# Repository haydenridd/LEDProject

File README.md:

# LEDProject
Repository for LED controller.

Casey if you're reading this yes it's the right repo.

If this worked then I sort of understand how to use this tool

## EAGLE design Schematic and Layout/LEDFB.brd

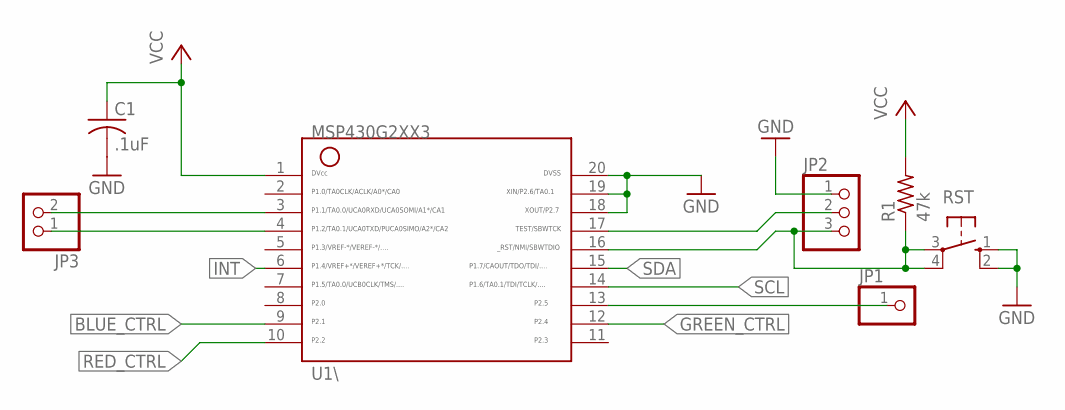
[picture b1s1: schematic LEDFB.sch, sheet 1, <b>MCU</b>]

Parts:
C1: .1uF; C0805
JP1: PINHD-1X1; 1X01
JP2: PINHD-1X3; 1X03
JP3: PINHD-1X2; 1X02
R1: 47k; R0805
RST: 10-XX; B3F-10XX
U1\: G2XX3---PW20; PW20

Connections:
BLUE_CTRL: U1\.9; also elsewhere on the board
GND: C1.2, JP2.1, RST.1 (S), RST.2 (S1), U1\.18, U1\.19, U1\.20; also elsewhere on the board
GREEN_CTRL: U1\.12; also elsewhere on the board
INT: U1\.6; also elsewhere on the board
unnamed: JP3.2, U1\.3
unnamed: JP3.1, U1\.4
unnamed: JP1.1, U1\.13
unnamed: JP2.2, U1\.17
unnamed: JP2.3, R1.1, RST.3, RST.4 (P1), U1\.16
RED_CTRL: U1\.10; also elsewhere on the board
SCL: U1\.14; also elsewhere on the board
SDA: U1\.15; also elsewhere on the board
VCC: C1.1, R1.2, U1\.1; also elsewhere on the board

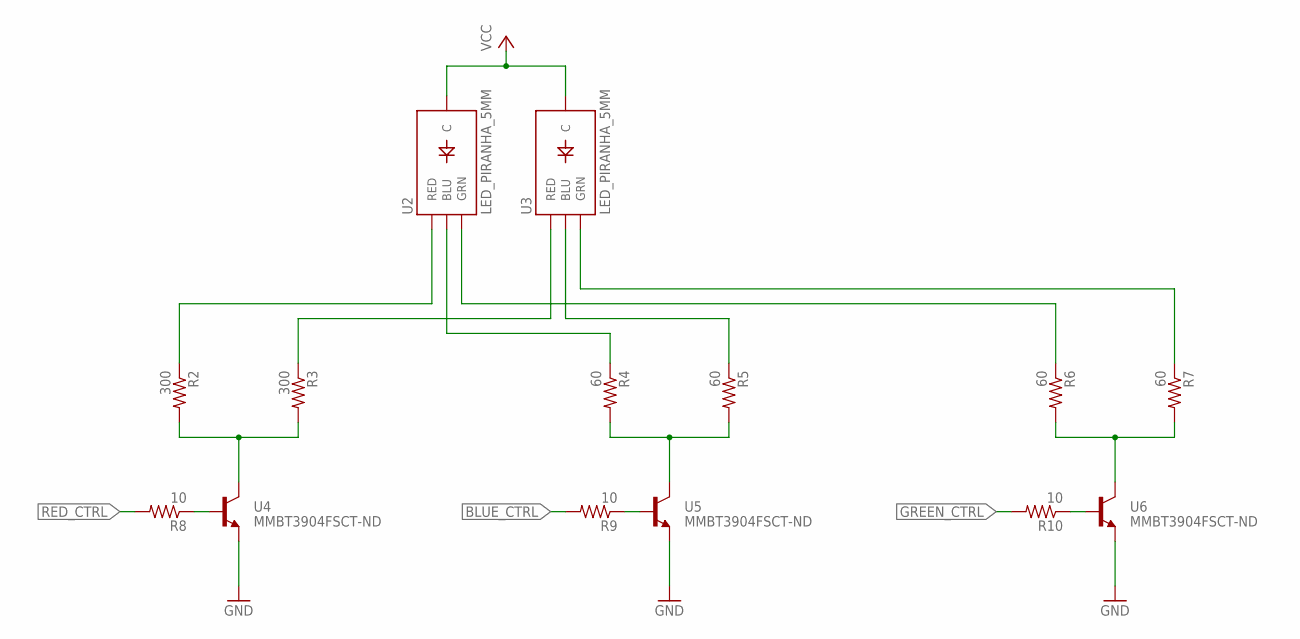
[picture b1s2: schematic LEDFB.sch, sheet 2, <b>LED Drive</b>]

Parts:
R2, R3: 300; R0805
R4, R5, R6, R7: 60; R0805
R8, R9, R10: 10; R0805
U2, U3: LED_PIRANHA_5MM
U4, U5, U6: MMBT3904FSCT-ND; SOT-23

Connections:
BLUE_CTRL: R9.2; also elsewhere on the board
GND: U4.2 (E), U5.2 (E), U6.2 (E); also elsewhere on the board
GREEN_CTRL: R10.2; also elsewhere on the board
unnamed: R2.1, U2.R (RED)
unnamed: R3.1, U3.R (RED)
unnamed: R2.2, R3.2, U4.3 (C)
unnamed: R4.1, U2.B (BLU)
unnamed: R8.1, U4.1 (B)
unnamed: R9.1, U5.1 (B)
unnamed: R10.1, U6.1 (B)
unnamed: R5.1, U3.B (BLU)
unnamed: R4.2, R5.2, U5.3 (C)
unnamed: R6.2, R7.2, U6.3 (C)
unnamed: R6.1, U2.G (GRN)
unnamed: R7.1, U3.G (GRN)
RED_CTRL: R8.2; also elsewhere on the board
VCC: U2.C, U3.C; also elsewhere on the board

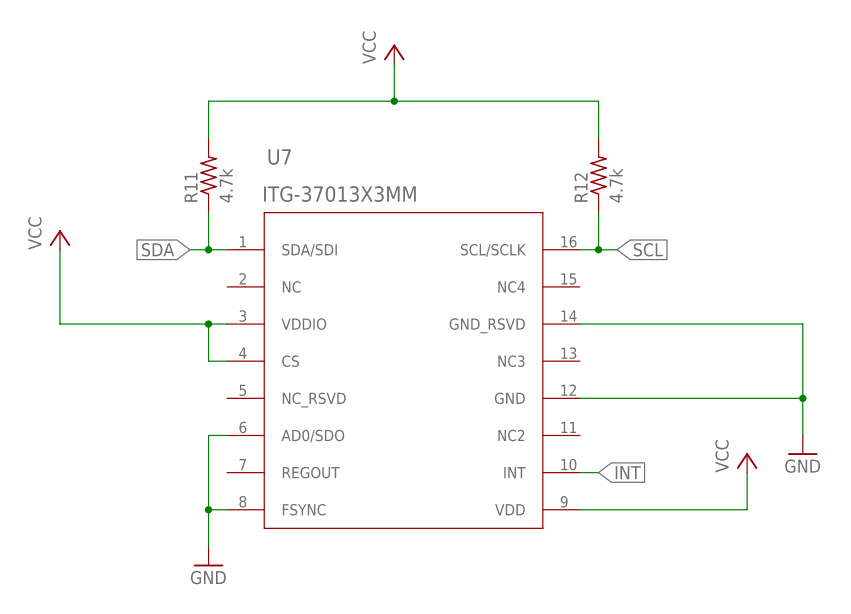
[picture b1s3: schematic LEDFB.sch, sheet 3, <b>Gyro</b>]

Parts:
R11, R12: 4.7k; M0805
U7: ITG-37013X3MM; QFN-16

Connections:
GND: U7.6 (AD0/SDO), U7.8 (FSYNC), U7.12 (GND), U7.14 (GND_RSVD); also elsewhere on the board
INT: U7.10 (INT); also elsewhere on the board
NC3: U7.13 (NC3)
NC4: U7.15 (NC4)
NC_RSVD: U7.5 (NC_RSVD)
SCL: R12.1, U7.16 (SCL/SCLK); also elsewhere on the board
SDA: R11.1, U7.1 (SDA/SDI); also elsewhere on the board
VCC: R11.2, R12.2, U7.3 (VDDIO), U7.4 (CS), U7.9 (VDD); also elsewhere on the board

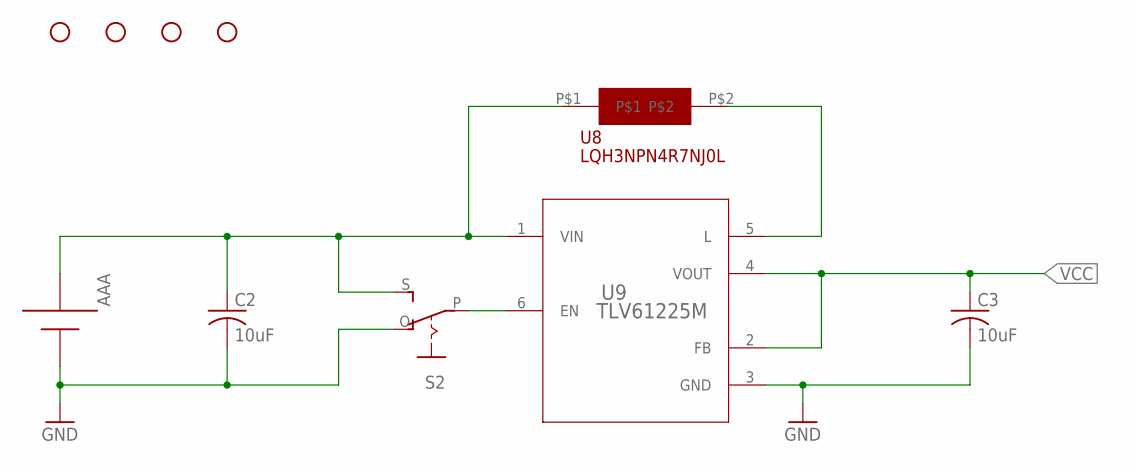
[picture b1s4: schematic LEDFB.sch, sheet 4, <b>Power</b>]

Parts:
AAA: AAA; 12BH412
C2, C3: 10uF; C0805
H1, H2, H3, H4: STAND-OFF
S2: EG1218S; EG1218
U8: LQH3NPN4R7NJ0; 1212
U9: TLV61225M; DCK0006A_M

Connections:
GND: AAA.-, C2.2, C3.2, S2.O, U9.3 (GND); also elsewhere on the board
unnamed: AAA.+, C2.1, S2.S, U8.P$1, U9.1 (VIN)
unnamed: S2.P, U9.6 (EN)
unnamed: U8.P$2, U9.5 (L)
VCC: C3.1, U9.2 (FB), U9.4 (VOUT); also elsewhere on the board

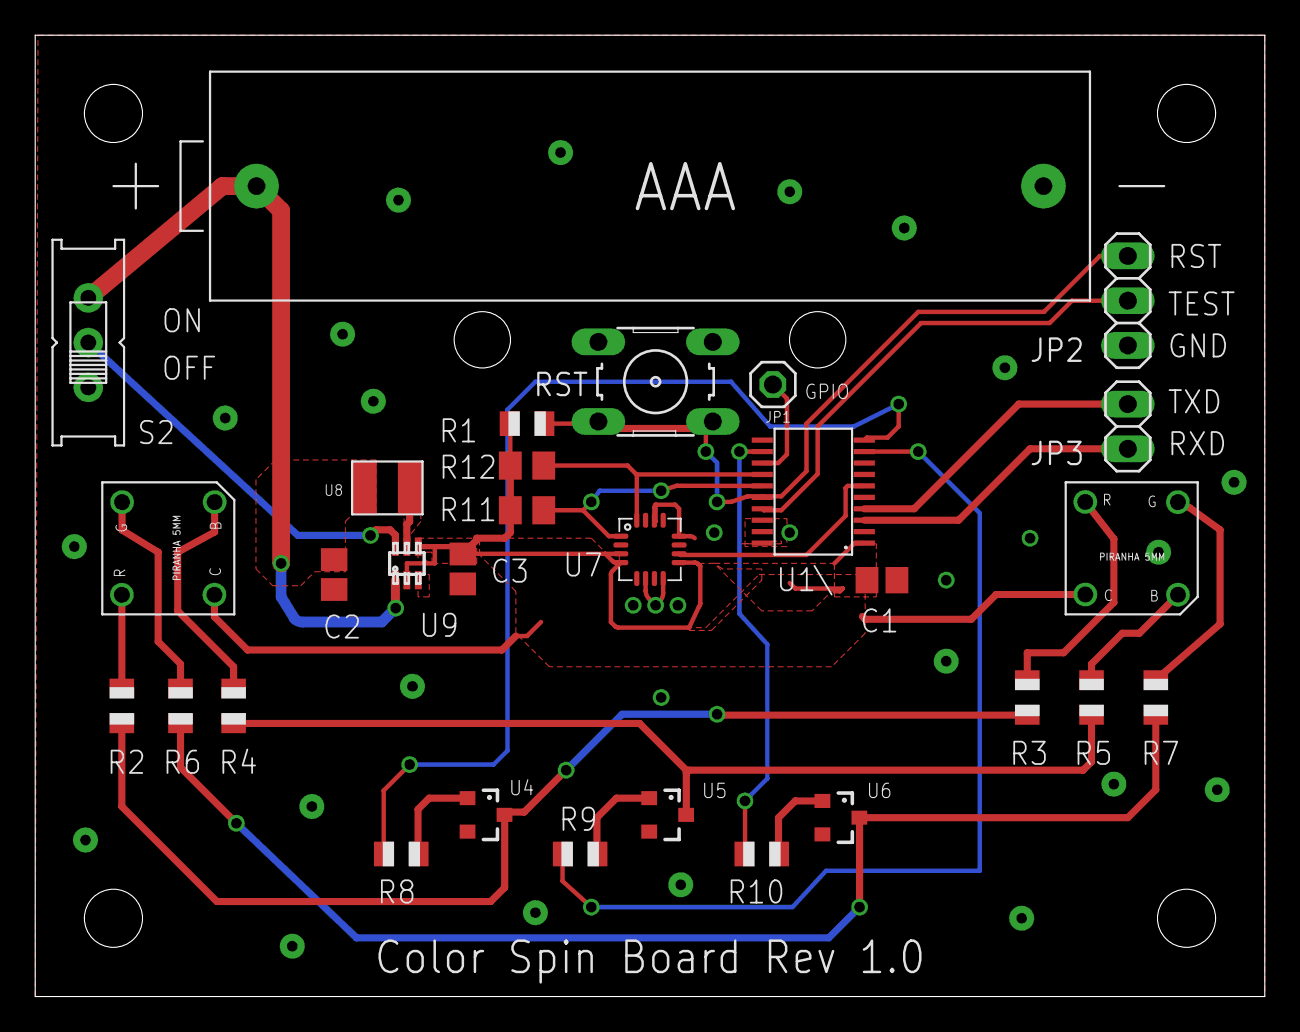
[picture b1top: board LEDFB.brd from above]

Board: 2 copper layers, 69.8 x 54.6 mm, 34 parts (0 on the bottom side), 28 nets.

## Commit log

2016-04-14 Updated readme, testing initial commit
2016-04-14 Added blank eagle schematic
2016-04-14 First Revision
2016-04-14 Update SpinCode.ino
    Removed commented debugging code
2016-04-15 Update SpinCode.ino
    Removed redundant abs()
2016-04-15 Started schematic, finished MSP430 connections
2016-04-15 Testing upload
2016-04-15 Testing commit
2016-04-15 Added library with MMBT3904 NPN Transistor
2016-04-15 Added additional schematic pages and wired the LEDs
2016-04-15 Added libary for 5mm Piranna LED package
2016-04-15 Re-organized, we aren't savages!
2016-04-21 Deleted to link with Energia Folder
2016-04-21 Re-added with Energia linked folder
2016-04-21 Created a sketch that calibrates the ITG3701 and performs basic testing
2016-04-21 Created a new overall project sketch that utilizes the new gyro (not yet tested)
2016-04-21 Reorg
2016-04-23 Added schematic for TI part
2016-04-23 Added itg3701 library, added a gitignore document to ignore autosave files, added reference docs
2016-04-24 Added tlv61225 eagle library
2016-04-24 Changed stuff
2016-04-26 Completed first rev of layout
2016-04-26 Increased board size to accomidate battery holder size and added standoffs. Generated a BOM.
2016-04-26 Deleted files and renamed BOM
2016-04-26 Fixed ground plane issue
2016-04-27 Changed some spacings and sizes, removed some vias, and generated GERBERS
2016-04-27 Added order receipts
2016-04-29 Started CAD model for enclosure
2016-05-05 Fixed ITG soldermask :(

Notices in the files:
parts and their libraries:
SparkFun-LED: Licensing: Creative Commons ShareAlike 4.0 International - https://creativecommons.org/licenses/by-sa/4.0
